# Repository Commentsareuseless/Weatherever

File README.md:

# Weather-ever
Simple weather station, to monitor wind speed, temperature and humidity

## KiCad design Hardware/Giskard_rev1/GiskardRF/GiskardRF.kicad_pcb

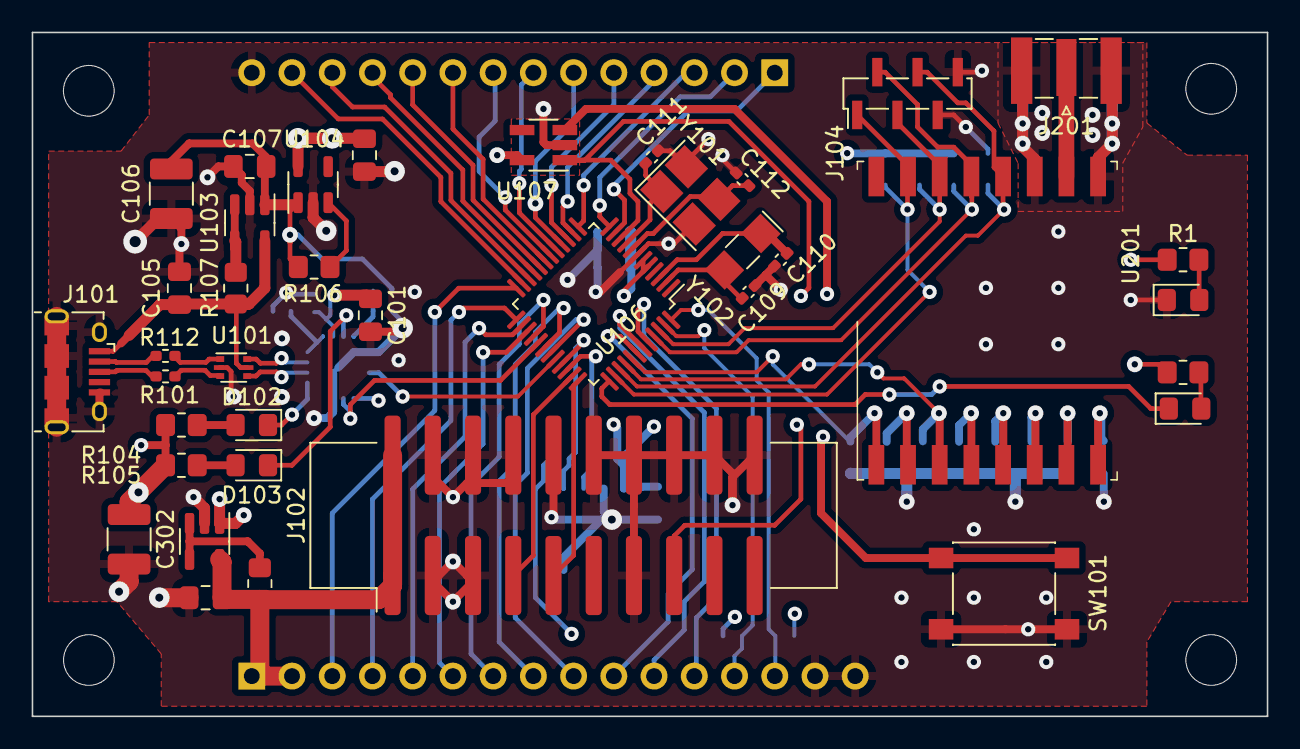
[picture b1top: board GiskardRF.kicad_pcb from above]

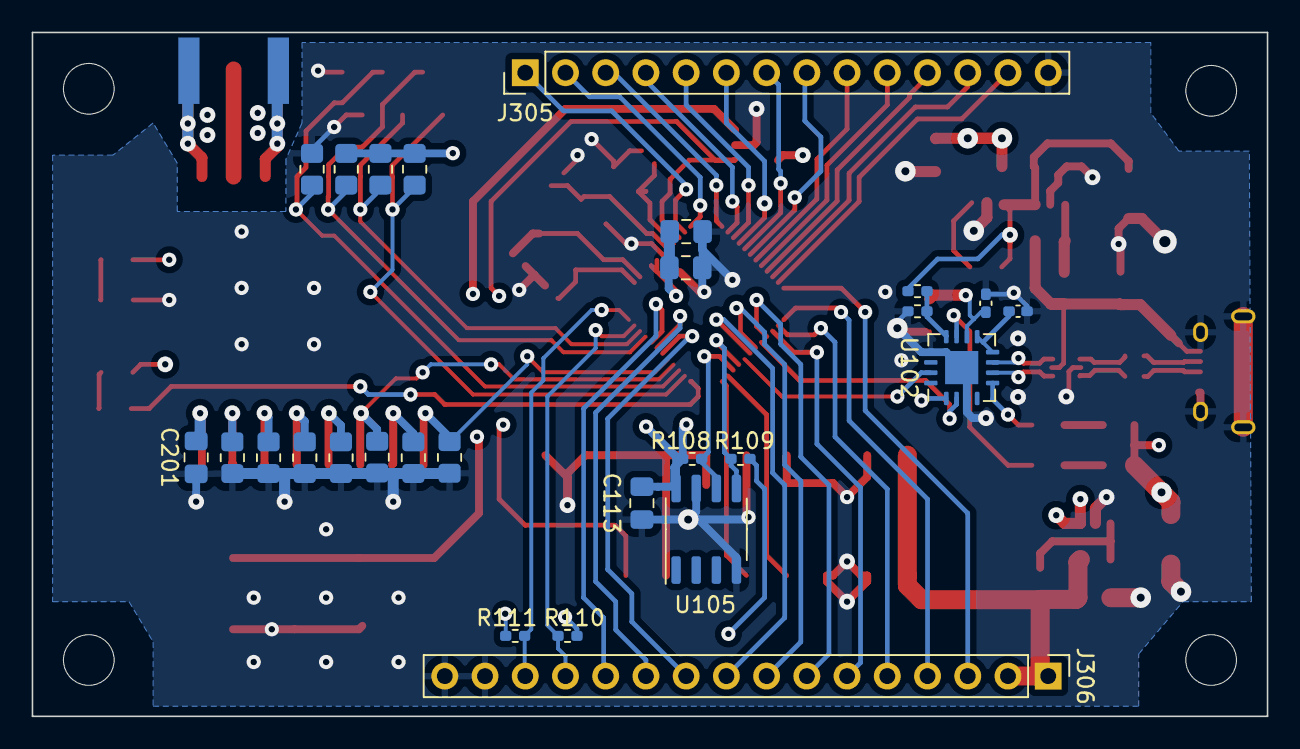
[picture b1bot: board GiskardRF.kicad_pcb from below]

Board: 4 copper layers, 78.0 x 43.2 mm, 69 parts (27 on the bottom side), 72 nets.

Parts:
C101: 4u7; C_0805_2012Metric_Pad1.18x1.45mm_HandSolder
C102, C104: 100n; C_0402_1005Metric_Pad0.74x0.62mm_HandSolder
C105, C108, C301: 1u; C_0805_2012Metric_Pad1.18x1.45mm_HandSolder
C106, C302: 100u; C_1210_3225Metric_Pad1.33x2.70mm_HandSolder
C107, C113, C115, C201: 100n; C_0805_2012Metric_Pad1.18x1.45mm_HandSolder
C109, C110: 20p; C_0402_1005Metric_Pad0.74x0.62mm_HandSolder
C111, C112: 13p; C_0402_1005Metric_Pad0.74x0.62mm_HandSolder
C114: 10u; C_0805_2012Metric_Pad1.18x1.45mm_HandSolder
D1: PWR_LED; D_0805_2012Metric_Pad1.15x1.40mm_HandSolder
D101: ERR_LED; D_0805_2012Metric_Pad1.15x1.40mm_HandSolder
D102: RX_LED; D_0805_2012Metric_Pad1.15x1.40mm_HandSolder
D103: TX_LED; D_0805_2012Metric_Pad1.15x1.40mm_HandSolder
H101, H102, H103, H104: MountingHole; MountingHole_3.2mm_M3
J101: USB_B_Micro; USB_Micro-B_Amphenol_10118194_Horizontal
J102: Conn_ARM_JTAG_SWD_20; IDC-Header_2x10_P2.54mm_Vertical_SMD
J104: Test pins COMM1; PinSocket_1x06_P1.27mm_Vertical_SMD_Pin1Left
J201: SMA6252A23G50; SMA_Samtec_SMA-J-P-X-ST-EM1_EdgeMount
J305: Conn_01x14; PinHeader_1x14_P2.54mm_Vertical
J306: Conn_01x16; PinHeader_1x16_P2.54mm_Vertical
R1, R102, R104, R105: 330; R_0805_2012Metric_Pad1.20x1.40mm_HandSolder
R101, R112: 27; R_0402_1005Metric_Pad0.72x0.64mm_HandSolder
R103: 4k7; R_0402_1005Metric_Pad0.72x0.64mm_HandSolder
R106: 2k; R_0805_2012Metric_Pad1.20x1.40mm_HandSolder
R107, R301: 10k; R_0805_2012Metric_Pad1.20x1.40mm_HandSolder
R108, R109, R110, R111: 3k3; R_0402_1005Metric_Pad0.72x0.64mm_HandSolder
R113: 10k; R_0402_1005Metric_Pad0.72x0.64mm_HandSolder
R201, R202, R203, R204, R206, R207, R208, R209, R210, R211: 20k; R_0805_2012Metric_Pad1.20x1.40mm_HandSolder
R205: 51k; R_0805_2012Metric_Pad1.20x1.40mm_HandSolder
SW101: RESET; SW_Push_1P1T_NO_6x6mm_H9.5mm
U101: USBLC6-2P6; SOT-666
U102: FT230XQ; QFN-16-1EP_4x4mm_P0.65mm_EP2.1x2.1mm
U103, U303: AP22802AW5-7; SOT-23-5
U104: AP2127K-3.3; SOT-23-5
U105: M24C16-RM; SO-8_3.9x4.9mm_P1.27mm
U106: STM32G070CBTx; LQFP-48_7x7mm_P0.5mm
U107: APX823; SOT-23-5_HandSoldering
U201: RFM69HW; HOPERF_RFM69HW
Y101: 3225-16M-SR 16MHz 9pF; Crystal_SMD_SeikoEpson_FA238-4Pin_3.2x2.5mm_HandSoldering
Y102: 32.768K-CFPX217; Crystal_SMD_MicroCrystal_CC7V-T1A-2Pin_3.2x1.5mm_HandSolder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

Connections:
+3V3: C101.1, C102.1, C108.1, C113.1, C114.1, C115.1, C201.2, C302.1, R1.1, R102.1, R104.1, R105.1, R108.1, R109.1, R110.1, R111.1, R202.1, R203.1, R204.1, U102.1 (VCCIO), U102.10 (VCC), U104.5 (VOUT), U105.8 (VCC), U106.5 (VREF+), U106.6 (VDD), U107.5 (VCC), U201.8 (3.3V), U303.1 (OUT)
+5V: C106.1, C107.1, R103.1, R106.2, U103.1 (OUT), U104.1 (VIN)
/5V_USB: C105.1, J101.1 (VBUS), R107.1, U101.5 (VBUS), U103.5 (IN)
/CON_PWR: C301.1, J102.1 (VTREF), J102.2 (VCC/NC), J306.1, J306.2, R301.1, U303.5 (IN)
/GPIO_PA0: J305.1, U106.11 (PA0)
/GPIO_PA1: J305.2, U106.12 (PA1)
/GPIO_PA2: J305.3, U106.13 (PA2)
/GPIO_PA3: J305.4, U106.14 (PA3)
/GPIO_PA4: J305.5, U106.15 (PA4)
/GPIO_PA8: J306.7, U106.28 (PA8)
/GPIO_PB0: J305.9, U106.19 (PB0)
/GPIO_PB1: J305.10, U106.20 (PB1)
/GPIO_PB2: J305.11, U106.21 (PB2)
/GPIO_PB3: J306.10, U106.42 (PB3)
/GPIO_PB4: J306.11, U106.43 (PB4)
/GPIO_PB5: J306.12, U106.44 (PB5)
/GPIO_PB10: J305.12, U106.22 (PB10)
/GPIO_PB11: J305.13, U106.23 (PB11)
/GPIO_PB12: J306.3, U106.24 (PB12)
/GPIO_PB13: J306.4, U106.25 (PB13)
/GPIO_PB14: J306.5, U106.26 (PB14)
/GPIO_PB15: J306.6, U106.27 (PB15)
/GPIO_PC6: J306.8, U106.30 (PC6)
/GPIO_PC7: J306.9, U106.31 (PC7)
/HF_OSC_IN: C112.1, U106.8 (PF0), Y101.3
/HF_OSC_OUT: C111.1, U106.9 (PF1), Y101.1
/I2C1_SCL: J306.13, R110.2, U106.47 (PB8)
/I2C1_SDA: J306.14, R111.2, U106.48 (PB9)
/I2C2_SCL_MEM: R109.2, U105.5 (SDA), U106.33 (PA11/PA9)
/I2C2_SDA_MEM: R108.2, U105.6 (SCL), U106.34 (PA12/PA10)
/LF_OSC_IN: C109.1, U106.2 (PC14), Y102.2
/LF_OSC_OUT: C110.1, U106.3 (PC15), Y102.1
/RF_FIFO_F_NE: R207.2, U106.40 (PD2), U201.3 (DIO1)
/RF_RESET: R205.2, U106.41 (PD3), U201.1 (RESET)
/RX_LED: D102.1 (K), U102.5 (CBUS2)
/RadioComm1/ANT_OUT: J201.1 (In), U201.10 (ANA)
/RadioComm1/RF_DIO0: R206.2, U201.2 (DIO0)
/RadioComm1/RF_DIO2: R208.2, U201.4 (DIO2)
/RadioComm1/RF_DIO3: R209.2, U201.5 (DIO3)
/RadioComm1/RF_DIO4: R210.2, U201.6 (DIO4)
/RadioComm1/RF_DIO5: R211.2, U201.7 (DIO5)
/SPI1_MISO: J305.7, U106.17 (PA6)
/SPI1_MOSI: J305.8, U106.18 (PA7)
/SPI1_SCK: J305.6, U106.16 (PA5)
/SPI2_MISO: J104.2, R202.2, U106.45 (PB6), U201.13 (MISO)
/SPI2_MOSI: J104.3, R203.2, U106.46 (PB7), U201.14 (MOSI)
/SPI2_NSS: J104.1, R204.2, U106.38 (PD0), U201.15 (NSS)
/SPI2_SCK: J104.4, R201.2, U106.39 (PD1), U201.12 (SCK)
/SW_CLK: J102.9 (TCK/SWDCLK), U106.36 (PA14)
/SW_DIO: J102.7 (TMS/SWDIO), U106.35 (PA13)
/TX_LED: D103.1 (K), U102.11 (CBUS1)
/USART1_RX: U102.15 (TXD), U106.32 (PA10/NC)
/USART1_TX: U102.2 (RXD), U106.29 (PA9/NC)
/USB_D+: J101.3 (D+), R101.2
/USB_D-: J101.2 (D-), R112.1
/USB_D_S+: U101.4 (I/O2), U102.6 (USBDP)
/USB_D_S-: U101.6 (I/O1), U102.7 (USBDM)
/USB_RES+: R101.1, U101.3 (I/O2)
/USB_RES-: R112.2, U101.1 (I/O1)
/~ERR_LED: D101.1 (K), U106.37 (PA15)
/~RESET: J102.15 (~SRST), U106.10 (NRST), U107.1 (~RESET)
GNDD: C101.2, C102.2, C104.2, C105.2, C106.2, C107.2, C108.2, C109.2, C110.2, C111.2, C112.2, C113.2, C114.2, C115.2, C201.1, C301.2, C302.2, D1.1 (K), J101.5 (GND), J101.6 (Shield), J102.3 (~TRST), J102.4 (GND), J102.5 (TDI), J102.6 (GND), J102.8 (GND), J102.10 (GND), J102.12 (GND), J102.13 (TDO/SWO), J102.14 (GND), J102.16 (GND), J102.18 (GND), J102.20 (GND), J104.5, J104.6, J201.2 (Ext), J305.14, J306.15, J306.16, R113.2, R201.1, R205.1, R206.1, R207.1, R208.1, R209.1, R210.1, R211.1, SW101.1, SW101.2, U101.2 (GND), U102.3 (GND), U102.13 (GND), U102.17 (GND), U103.2 (GND), U104.2 (GND), U105.4 (GND), U105.7 (~WC), U106.7 (VSS), U107.2 (GND), U201.9 (GND), U201.11 (GND), U303.2 (GND), Y101.2, Y101.4
unnamed: D1.2 (A), R1.2
unnamed: D101.2 (A), R102.2
unnamed: D102.2 (A), R104.2
unnamed: D103.2 (A), R105.2
unnamed: SW101.3 (K), SW101.4 (A), U107.3 (~MR)
unnamed: C104.1, U102.8 (3V3OUT), U102.9 (~RESET)
unnamed: R103.2, R113.1, U102.12 (CBUS0)
unnamed: R107.2, U103.3 (~FLG), U103.4 (EN)
unnamed: R106.1, U104.3 (EN)
unnamed: R301.2, U303.3 (~FLG), U303.4 (EN)

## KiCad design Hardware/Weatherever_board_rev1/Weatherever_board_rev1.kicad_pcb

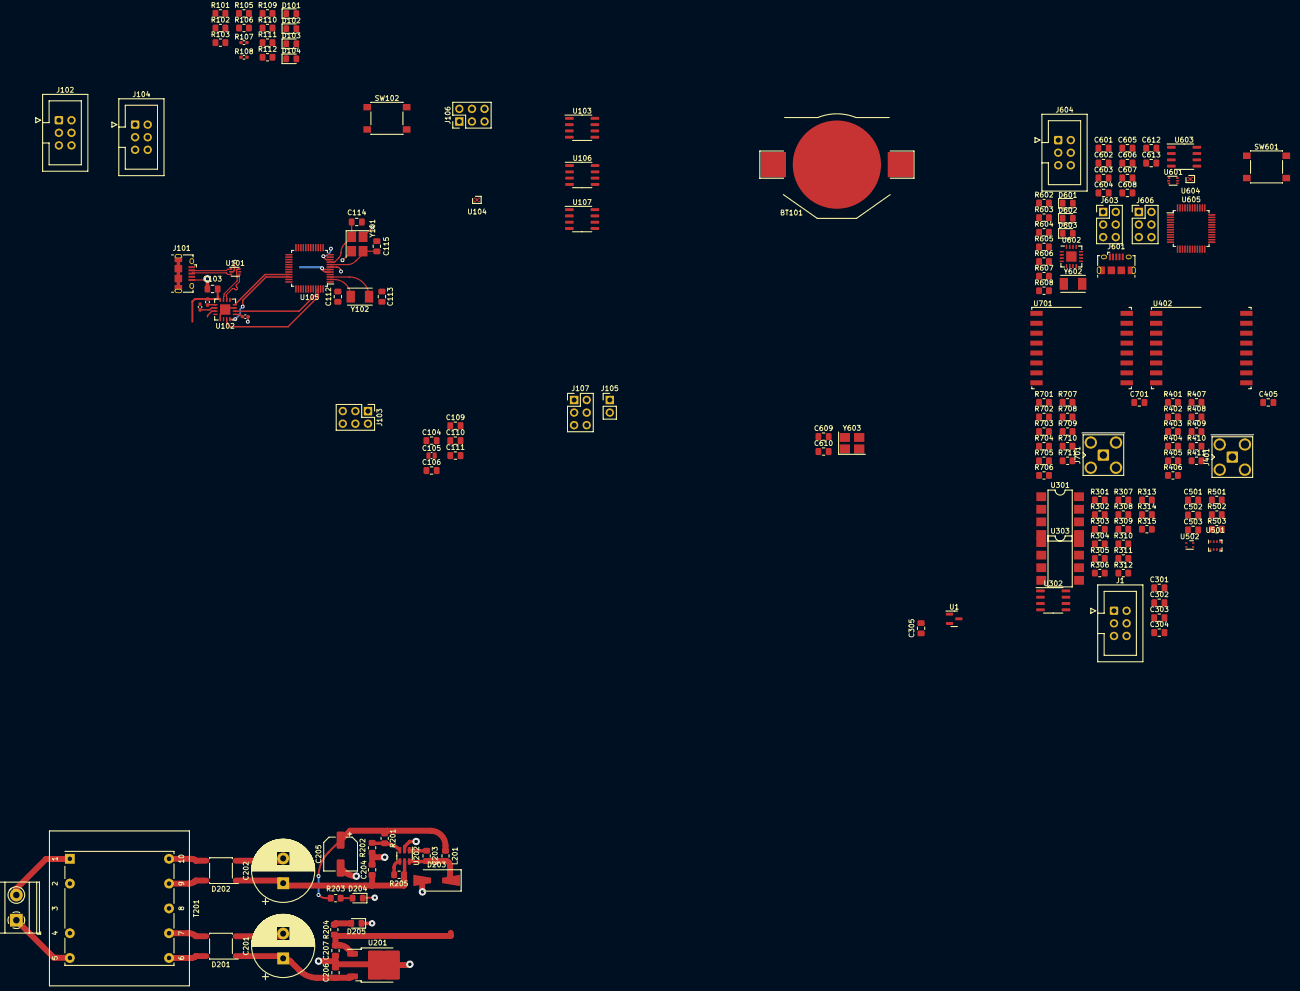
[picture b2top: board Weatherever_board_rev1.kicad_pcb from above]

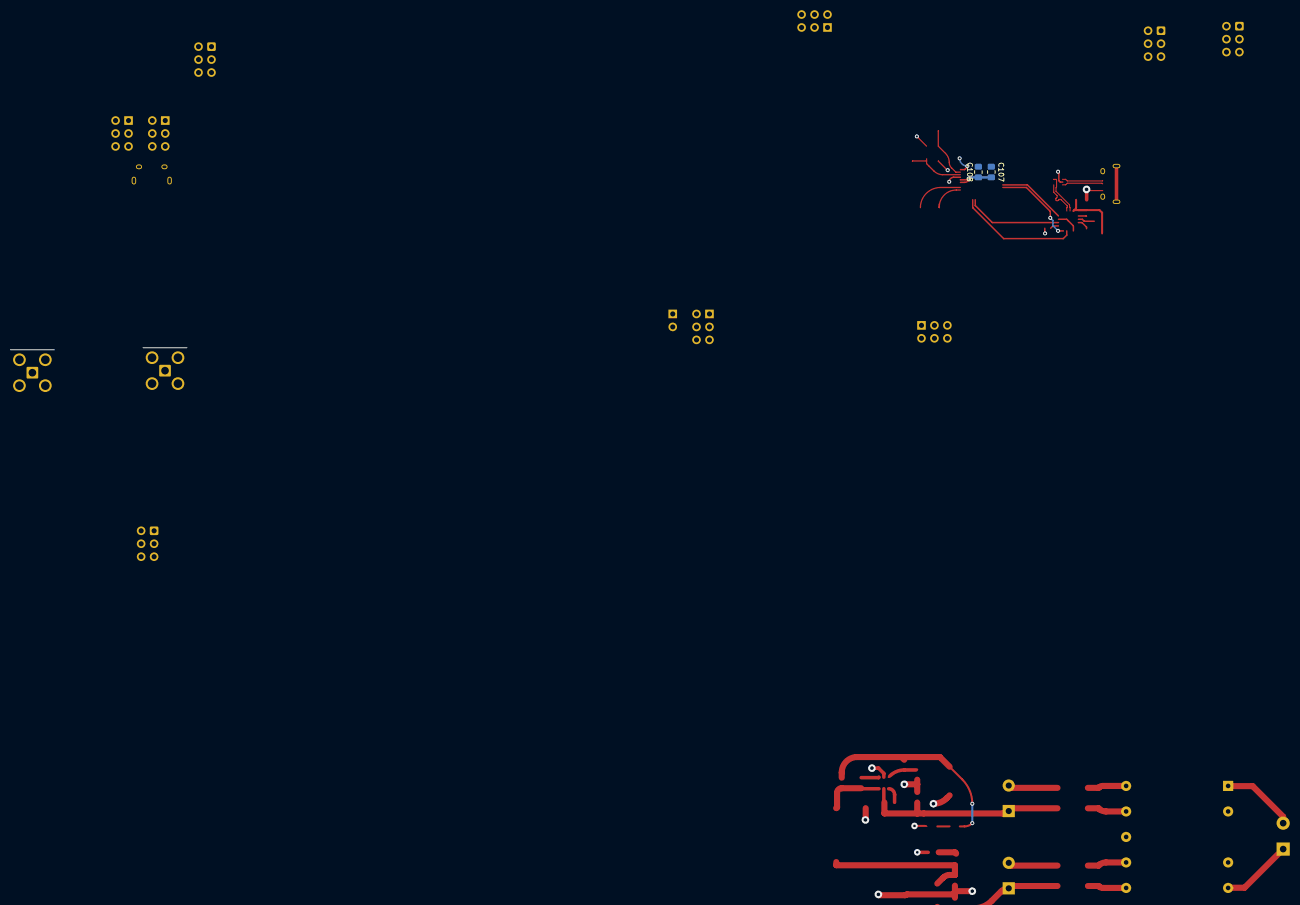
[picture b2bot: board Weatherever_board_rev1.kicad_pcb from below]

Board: 2 copper layers, 171 parts (2 on the bottom side), 118 nets.

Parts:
BT101: RTC_Bat; BatteryHolder_Keystone_3002_1x2032
C101, C102: 100n; C_0402_1005Metric_Pad0.74x0.62mm_HandSolder
C103, C106, C603, C606: 1u; C_0805_2012Metric_Pad1.18x1.45mm_HandSolder
C104, C107, C204, C604, C607: 10u; C_0805_2012Metric_Pad1.18x1.45mm_HandSolder
C105: 100n; C_0504_1310Metric_Pad0.83x1.28mm_HandSolder
C108, C109, C110, C111, C112, C113, C114, C115, C207, C301, C303, C305, C405, C501, C502, C503, C601, C602, C605, C608, C609, C610, C612, C613, C701: 100n; C_0805_2012Metric_Pad1.18x1.45mm_HandSolder
C201, C202: 1500u; CP_Radial_D12.5mm_P5.00mm
C203, C302, C304: 10n; C_0805_2012Metric_Pad1.18x1.45mm_HandSolder
C205: 100u; CP_Elec_6.3x5.4
C206: 330n; C_0805_2012Metric_Pad1.18x1.45mm_HandSolder
D101, D601: ERR_LED (RED); D_0805_2012Metric_Pad1.15x1.40mm_HandSolder
D102, D602: RX_LED; D_0805_2012Metric_Pad1.15x1.40mm_HandSolder
D103, D603: TX_LED; D_0805_2012Metric_Pad1.15x1.40mm_HandSolder
D104: CPU_PWR; D_0805_2012Metric_Pad1.15x1.40mm_HandSolder
D201, D202: AB4S; Diode_Bridge_Diotec_ABS
D203: STS130A; D_SMA-SMB_Universal_Handsoldering
D204: PWR_3V3; LED_0805_2012Metric_Pad1.15x1.40mm_HandSolder
D205: PWR_9V; LED_0805_2012Metric_Pad1.15x1.40mm_HandSolder
H101, H102, H103, H104, H105: MountingHole; MountingHole_3.2mm_M3
J1: ProbeConn; IDC-Header_2x03_P2.54mm_Vertical
J101, J601: USB_B_Micro; USB_Micro-B_Amphenol_10118194_Horizontal
J102: Expansion conn; IDC-Header_2x03_P2.54mm_Vertical
J103, J603: Test pins COMM1; PinHeader_2x03_P2.54mm_Vertical
J104, J604: DebugConn; IDC-Header_2x03_P2.54mm_Vertical
J105: Test pins Probe; PinHeader_1x02_P2.54mm_Vertical
J106, J606: Test pins COMM2; PinHeader_2x03_P2.54mm_Vertical
J107: Test pins I2C; PinHeader_2x03_P2.54mm_Vertical
J201: Mains (230V, 50Hz); TerminalBlock_Phoenix_MKDS-1,5-2-5.08_1x02_P5.08mm_Horizont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
J401, J701: SMA6252A23G50; SMA_Amphenol_901-143_Horizontal
L201: 2u2; L_0805_2012Metric_Pad1.15x1.40mm_HandSolder
R101, R103, R105, R106, R203, R603, R605, R606: 270; R_0805_2012Metric_Pad1.20x1.40mm_HandSolder
R102, R302, R501, R502, R503, R602, R604, R607: 2k; R_0805_2012Metric_Pad1.20x1.40mm_HandSolder
R104, R107: 2k; R_0402_1005Metric_Pad0.72x0.64mm_HandSolder
R108: 10k; R_0402_1005Metric_Pad0.72x0.64mm_HandSolder
R109, R110, R111, R112, R303, R310: 3k3; R_0805_2012Metric_Pad1.20x1.40mm_HandSolder
R201: 51k1; R_0805_2012Metric_Pad1.20x1.40mm_HandSolder
R202: 16k2; R_0805_2012Metric_Pad1.20x1.40mm_HandSolder
R204: 1k; R_0805_2012Metric_Pad1.20x1.40mm_HandSolder
R205, R608: 10k; R_0805_2012Metric_Pad1.20x1.40mm_HandSolder
R301: 330; R_0805_2012Metric_Pad1.20x1.40mm_HandSolder
R304, R313, R411, R705: 51k; R_0805_2012Metric_Pad1.20x1.40mm_HandSolder
R305, R306, R308, R309, R311, R314, R315, R401, R402, R403, R404, R405, R406, R407, R408, R409, R410, R701, R702, R703, R704, R706, R707, R708, R709, R710, R711: 20k; R_0805_2012Metric_Pad1.20x1.40mm_HandSolder
R307, R312: 100k; R_0805_2012Metric_Pad1.20x1.40mm_HandSolder
SW102, SW601: RESET; SW_Push_1P1T_NO_6x6mm_H9.5mm
T201: TEZ2.5/D230/10.5-10.5V; Transformer_Breve_TEZ-28x33
U1: ZXCT1009F; SOT-23
U101, U601: USBLC6-2P6; SOT-666
U102, U602: FT230XQ; QFN-16-1EP_4x4mm_P0.65mm_EP2.1x2.1mm
U103, U603: AOZ1312; SO-8_3.9x4.9mm_P1.27mm
U104, U604: NCP115AMX250TCG; OnSemi_XDFN4-1EP_1.0x1.0mm_EP0.52x0.52mm
U105, U605: STM32G030C8T6; LQFP-48_7x7mm_P0.5mm
U106, U107: M24C08-W; SO-8_3.9x4.9mm_P1.27mm
U201: L78M09CDT; TO-252-2
U202: AOZ1280CI; SOT-23-6
U301, U303: 6N137; SMDIP-8_W7.62mm
U302: LM393; SO-8_3.9x4.9mm_P1.27mm
U402, U701: RFM69HW; HOPERF_RFM69HW
U501: DPS310; Bosch_LGA-8_2x2.5mm_P0.65mm_ClockwisePinNumbering
U502: SHT4x; Sensirion_DFN-4_1.5x1.5mm_P0.8mm_SHT4x_NoCentralPad
Y101, Y603: 3225-16M-SR 16MHz 9pF; Crystal_SMD_TXC_7M-4Pin_3.2x2.5mm_HandSoldering
Y102, Y602: 32.768K-CFPX217; Crystal_SMD_TXC_7A-2Pin_5x3.2mm

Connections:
+3V3: C102.1, C103.1, C106.1, C107.1, C108.1, C109.1, C110.1, C205.1, C301.1, C303.1, C405.2, C501.1, C502.1, C503.1, C602.1, C603.1, C606.1, C607.1, C608.1, C701.2, J102.1, J104.1, J104.2, J604.1, J604.2, L201.2, R101.1, R102.1, R103.1, R104.1, R105.1, R106.1, R109.1, R110.1, R111.1, R112.1, R201.1, R203.1, R303.1, R310.1, R402.1, R403.1, R404.1, R501.2, R502.2, R503.2, R602.1, R603.1, R604.1, R605.1, R606.1, R702.1, R703.1, R704.1, U102.1 (VCCIO), U102.8 (3V3OUT), U104.1 (OUT), U105.5 (VREF+), U105.6 (VDD/VDDA), U106.3 (E2), U106.8 (Vcc), U107.8 (Vcc), U301.8 (VCC), U303.8 (VCC), U402.8 (3.3V), U501.6 (VDDIO), U501.8 (VDD), U502.3 (VDD), U602.1 (VCCIO), U602.8 (3V3OUT), U604.1 (OUT), U605.5 (VREF+), U605.6 (VDD/VDDA), U701.8 (3.3V)
+5V: C101.1, C105.1, C601.1, C605.1, R107.2, R607.2, U102.10 (VCC), U103.7 (OUT), U104.4 (IN), U602.10 (VCC), U603.7 (OUT), U604.4 (IN)
+9V: C207.1, C305.2, J102.5, R204.1, R301.1, R304.1, R305.1, R306.1, R311.1, R313.1, U1.2 (Vs+), U201.1 (OUT), U302.8 (V+)
/3V_Bat: BT101.1 (+), C111.1, U105.4 (VBAT)
/5V_USB: J101.1 (VBUS), R108.1, U101.5 (VBUS), U103.2 (IN), U103.4 (EN)
/CONN_VALID: R310.2, U105.39 (PD1), U303.6 (VO), U303.7 (EN)
/HF_OSC_IN: C115.1, U105.8 (PF0-OSC_IN), Y101.3
/HF_OSC_OUT: C114.1, U105.9 (PF1-OSC_OUT), Y101.1
/I2C1_SCL: J107.5, R111.2, R501.1, U105.29 (PA9), U501.4 (SCK), U502.2 (SCL)
/I2C1_SDA: J107.6, R112.2, R502.1, U105.32 (PA10), U501.3 (SDI), U502.1 (SDA)
/I2C2_SCL_MEM: J107.1, R109.2, R110.2, U105.25 (PB13), U106.6 (SCL), U107.6 (SCL)
/I2C2_SDA_MEM: J107.2, U105.26 (PB14), U106.5 (SDA), U107.5 (SDA)
/IsolatedFreqCnt/ConnCheck-: J1.1, J1.2, R301.2, U1.1 (Vs-)
/IsolatedFreqCnt/CurrentOut: R302.1, R314.2, U1.3 (Iout)
/IsolatedFreqCnt/NPN_OUT: J1.4, R304.2, R308.2
/LF_OSC_IN: C112.1, U105.2 (PC14-OSC32_IN), Y102.2
/LF_OSC_OUT: C113.1, U105.3 (PC15-OSC32_OUT), Y102.1
/PRS_RDY: U105.41 (PD3), U501.5 (SDO)
/PowerSupply/10V5AC_HI1: D201.4, T201.6 (SA)
/PowerSupply/10V5AC_HI2: D201.3, T201.7 (SB)
/PowerSupply/10V5AC_LO1: D202.4, T201.9 (SC)
/PowerSupply/10V5AC_LO2: D202.3, T201.10 (SD)
/PowerSupply/~15V_HI: C201.1, C206.1, D201.1 (+), U201.3 (IN)
/PowerSupply/~15V_LO: C202.1, C204.1, D202.1 (+), R205.1, U202.5 (VIN)
/RF_DIO_0: R409.2, U105.21 (PB2), U402.2 (DIO0)
/RF_DIO_1: R408.2, U105.22 (PB10), U402.3 (DIO1)
/RF_DIO_2: R407.2, U105.23 (PB11), U402.4 (DIO2)
/RF_DIO_3: R406.2, U105.24 (PB12), U402.5 (DIO3)
/RF_DIO_4: R405.2, U105.44 (PB5), U402.6 (DIO4)
/RF_DIO_5: R410.2, U105.43 (PB4), U402.7 (DIO5)
/RX_LED: D102.1 (K), U102.5 (CBUS2)
/RadioComm/ANT_OUT: J401.1 (In), U402.10 (ANA)
/RadioComm/RF_RESET: R411.2, U402.1 (RESET)
/SPI1_CS1: J103.2, R404.2, U105.19 (PB0), U402.15 (NSS)
/SPI1_CS2: J103.1, U105.20 (PB1)
/SPI1_MISO: J103.4, U105.17 (PA6), U402.13 (MISO)
/SPI1_MOSI: J103.3, R402.2, R403.2, U105.18 (PA7), U402.14 (MOSI)
/SPI1_SCK: J103.5, R401.2, U105.16 (PA5), U402.12 (SCK)
/SW_CLK: J104.3, U105.36 (PA14-BOOT0)
/SW_DIO: J104.4, U105.35 (PA13)
/TIM_IN: J105.1, R303.2, U105.38 (PD0), U301.6 (VO), U301.7 (EN)
/TX_LED: D103.1 (K), U102.11 (CBUS1)
/USART1_CTS: J106.4, U102.4 (~CTS), U105.33 (PA11)
/USART1_RTS: J106.3, U102.16 (~RTS), U105.34 (PA12)
/USART1_RX: J106.2, U102.15 (TXD), U105.46 (PB7)
/USART1_TX: J106.1, U102.2 (RXD), U105.45 (PB6)
/USART2_RX: J102.4, U105.14 (PA3)
/USART2_TX: J102.3, U105.13 (PA2)
/USB_D+: J101.3 (D+), U101.3 (I/O2)
/USB_D-: J101.2 (D-), U101.1 (I/O1)
/USB_D_S+: U101.4 (I/O2), U102.6 (USBDP)
/USB_D_S-: U101.6 (I/O1), U102.7 (USBDM)
/USB_Dongle/5V_USB: J601.1 (VBUS), R608.1, U601.5 (VBUS), U603.2 (IN), U603.4 (EN)
/USB_Dongle/HF_OSC_IN: C610.1, U605.8 (PF0-OSC_IN), Y603.3
/USB_Dongle/HF_OSC_OUT: C609.1, U605.9 (PF1-OSC_OUT), Y603.1
/USB_Dongle/LF_OSC_IN: C612.1, U605.2 (PC14-OSC32_IN), Y602.2
/USB_Dongle/LF_OSC_OUT: C613.1, U605.3 (PC15-OSC32_OUT), Y602.1
/USB_Dongle/RF_DIO_0: R706.2, U605.21 (PB2), U701.2 (DIO0)
/USB_Dongle/RF_DIO_1: R707.2, U605.22 (PB10), U701.3 (DIO1)
/USB_Dongle/RF_DIO_2: R708.2, U605.23 (PB11), U701.4 (DIO2)
/USB_Dongle/RF_DIO_3: R709.2, U605.24 (PB12), U701.5 (DIO3)
/USB_Dongle/RF_DIO_4: R710.2, U605.44 (PB5), U701.6 (DIO4)
/USB_Dongle/RF_DIO_5: R711.2, U605.43 (PB4), U701.7 (DIO5)
/USB_Dongle/RX_LED: D602.1 (K), U602.5 (CBUS2)
/USB_Dongle/RadioComm1/ANT_OUT: J701.1 (In), U701.10 (ANA)
/USB_Dongle/RadioComm1/RF_RESET: R705.2, U701.1 (RESET)
/USB_Dongle/SPI1_CS1: J603.2, R704.2, U605.19 (PB0), U701.15 (NSS)
/USB_Dongle/SPI1_CS2: J603.1, U605.20 (PB1)
/USB_Dongle/SPI1_MISO: J603.4, U605.17 (PA6), U701.13 (MISO)
/USB_Dongle/SPI1_MOSI: J603.3, R702.2, R703.2, U605.18 (PA7), U701.14 (MOSI)
/USB_Dongle/SPI1_SCK: J603.5, R701.2, U605.16 (PA5), U701.12 (SCK)
/USB_Dongle/SW_CLK: J604.3, U605.36 (PA14-BOOT0)
/USB_Dongle/SW_DIO: J604.4, U605.35 (PA13)
/USB_Dongle/TX_LED: D603.1 (K), U602.11 (CBUS1)
/USB_Dongle/USART1_CTS: J606.4, U602.4 (~CTS), U605.33 (PA11)
/USB_Dongle/USART1_RTS: J606.3, U602.16 (~RTS), U605.34 (PA12)
/USB_Dongle/USART1_RX: J606.2, U602.15 (TXD), U605.46 (PB7)
/USB_Dongle/USART1_TX: J606.1, U602.2 (RXD), U605.45 (PB6)
/USB_Dongle/USB_D+: J601.3 (D+), U601.4 (I/O2)
/USB_Dongle/USB_D-: J601.2 (D-), U601.6 (I/O1)
/USB_Dongle/USB_D_S+: U601.3 (I/O2), U602.6 (USBDP)
/USB_Dongle/USB_D_S-: U601.1 (I/O1), U602.7 (USBDM)
/USB_Dongle/~ERR_LED: D601.1 (K), U605.40 (PD2)
/USB_Dongle/~RESET: C604.1, R602.2, SW601.2, U605.10 (NRST)
/~ERR_LED: D101.1 (K), U105.40 (PD2)
/~RESET: C104.1, R102.2, SW102.2, U105.10 (NRST)
GND1: C201.2, C206.2, C207.2, C305.1, D201.2 (-), D205.1 (K), J1.5, J1.6, J102.6, R302.2, R309.2, R315.2, U201.2 (GND), U302.4 (V-)
GNDD: BT101.2 (-), C101.2, C102.2, C103.2, C104.2, C105.2, C106.2, C107.2, C108.2, C109.2, C110.2, C111.2, C112.2, C113.2, C114.2, C115.2, C202.2, C204.2, C205.2, C301.2, C303.2, C405.1, C501.2, C502.2, C503.2, C601.2, C602.2, C603.2, C604.2, C605.2, C606.2, C607.2, C608.2, C609.2, C610.2, C612.2, C613.2, C701.1, D104.1 (K), D202.2 (-), D203.2 (A), D204.1 (K), J101.5 (GND), J101.6 (Shield), J102.2, J103.6, J104.5, J104.6, J105.2, J106.6, J107.3, J107.4, J401.2 (Ext), J601.5 (GND), J601.6 (Shield), J603.6, J604.5, J604.6, J606.6, J701.2 (Ext), R202.2, R401.1, R405.1, R406.1, R407.1, R408.1, R409.1, R410.1, R411.1, R701.1, R705.1, R706.1, R707.1, R708.1, R709.1, R710.1, R711.1, SW102.1, SW601.1, U101.2 (GND), U102.3 (GND), U102.13 (GND), U102.17 (GND), U103.1 (GND), U104.2 (GND), U104.5 (GND), U105.7 (VSS/VSSA), U106.4 (Vss), U106.7 (WC), U107.3 (E2), U107.4 (Vss), U107.7 (WC), U202.2 (GND), U301.5 (GND), U303.5 (GND), U402.9 (GND), U402.11 (GND), U501.1 (GND), U501.7 (GND), U502.4 (VSS), U601.2 (GND), U602.3 (GND), U602.13 (GND), U602.17 (GND), U603.1 (GND), U604.2 (GND), U604.5 (GND), U605.7 (VSS/VSSA), U701.9 (GND), U701.11 (GND), Y101.2, Y101.4, Y603.2, Y603.4
unnamed: D101.2 (A), R103.2
unnamed: D102.2 (A), R105.2
unnamed: D103.2 (A), R106.2
unnamed: D104.2 (A), R101.2
unnamed: C203.2, D203.1 (K), L201.1, U202.6 (LX)
unnamed: D204.2 (A), R203.2
unnamed: D205.2 (A), R204.2
unnamed: D601.2 (A), R603.2
unnamed: D602.2 (A), R605.2
unnamed: D603.2 (A), R606.2
unnamed: J201.1, T201.5 (AB)
unnamed: J201.2, T201.1 (AA)
unnamed: R104.2, U102.9 (~RESET)
unnamed: R108.2, U103.5 (~OC)
unnamed: R107.1, U104.3 (EN)
unnamed: C203.1, U202.1 (BST)
unnamed: R205.2, U202.4 (EN)
unnamed: R201.2, R202.1, U202.3 (FB)
unnamed: R306.2, U301.2 (A)
unnamed: C302.1, R307.1, U301.3 (C), U302.7
unnamed: C304.2, R312.2, R314.1, U302.3 (+)
unnamed: R313.2, R315.1, U302.2 (-)
unnamed: C302.2, R307.2, R308.1, U302.5 (+)
unnamed: R305.2, R309.1, U302.6 (_)
unnamed: R311.2, U303.2 (A)
unnamed: C304.1, R312.1, U302.1, U303.3 (C)
unnamed: R503.1, U501.2 (CSB)
unnamed: R604.2, U602.9 (~RESET)
unnamed: R608.2, U603.5 (~OC)
unnamed: R607.1, U604.3 (EN)

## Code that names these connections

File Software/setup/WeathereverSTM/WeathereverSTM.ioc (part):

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Mcu.Name=STM32G030C(6-8)Tx
Mcu.Package=LQFP48
Mcu.UserName=STM32G030C8Tx
PA10.GPIOParameters=GPIO_Pu
PA10.GPIO_Pu=GPIO_PULLUP
PA10.Mode=I2C
PA10.Signal=I2C1_SDA
PA11\ [PA9].Mode=CTS_RTS
PA11\ [PA9].Signal=USART1_CTS
PA12\ [PA10].Mode=CTS_RTS
PA12\ [PA10].Signal=USART1_RTS
PA13.Mode=Serial_Wire
PA13.Signal=SYS_SWDIO
PA14-BOOT0.Mode=Serial_Wire
PA14-BOOT0.Signal=SYS_SWCLK
PA2.Mode=Asynchronous
PA2.Signal=USART2_TX
PA3.Mode=Asynchronous
PA3.Signal=USART2_RX
PA5.Mode=Full_Duplex_Master
PA5.Signal=SPI1_SCK
PA6.Mode=Full_Duplex_Master
PA6.Signal=SPI1_MISO
PA7.Mode=Full_Duplex_Master
PA7.Signal=SPI1_MOSI
PA9.GPIOParameters=GPIO_Pu
PA9.GPIO_Pu=GPIO_PULLUP
PA9.Mode=I2C
PA9.Signal=I2C1_SCL
PB0.Signal=GPIO_Output
PB1.Signal=GPIO_Output
PB10.Signal=GPIO_Input
PB13.GPIOParameters=GPIO_Pu
PB13.GPIO_Pu=GPIO_PULLUP
PB13.Mode=I2C
PB13.Signal=I2C2_SCL
PB14.GPIOParameters=GPIO_Pu
PB14.GPIO_Pu=GPIO_PULLUP
PB14.Mode=I2C
PB14.Signal=I2C2_SDA
PB2.Signal=GPIO_Input
PB3.Signal=GPIO_Input
PB6.Mode=Asynchronous
PB6.Signal=USART1_TX
PB7.Mode=Asynchronous
PB7.Signal=USART1_RX
PC14-OSC32_IN\ (PC14).Mode=LSE-External-Oscillator
PC14-OSC32_IN\ (PC14).Signal=RCC_OSC32_IN
PC15-OSC32_OUT\ (PC15).Mode=LSE-External-Oscillator
PC15-OSC32_OUT\ (PC15).Signal=RCC_OSC32_OUT
PD0.Signal=S_TIM16_CH1
PD1.Signal=GPIO_Input
PD2.Signal=GPIO_Input
PD3.Signal=GPIO_Input
PF0-OSC_IN\ (PF0).Mode=HSE-External-Oscillator
PF0-OSC_IN\ (PF0).Signal=RCC_OSC_IN
PF1-OSC_OUT\ (PF1).Mode=HSE-External-Oscillator
PF1-OSC_OUT\ (PF1).Signal=RCC_OSC_OUT
RCC.HSE_VALUE=16000000
RCC.SYSCLKFreq_VALUE=32000000
RCC.SYSCLKSource=RCC_SYSCLKSOURCE_PLLCLK
board=custom

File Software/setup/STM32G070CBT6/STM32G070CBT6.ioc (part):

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Mcu.Name=STM32G070CBTx
Mcu.Package=LQFP48
Mcu.UserName=STM32G070CBTx
PA10.Mode=Asynchronous
PA10.Signal=USART1_RX
PA11\ [PA9].Mode=I2C
PA11\ [PA9].Signal=I2C2_SCL
PA12\ [PA10].Mode=I2C
PA12\ [PA10].Signal=I2C2_SDA
PA13.Mode=Serial_Wire
PA13.Signal=SYS_SWDIO
PA14-BOOT0.Mode=Serial_Wire
PA14-BOOT0.Signal=SYS_SWCLK
PA5.Mode=Full_Duplex_Master
PA5.Signal=SPI1_SCK
PA6.Mode=Full_Duplex_Master
PA6.Signal=SPI1_MISO
PA7.Mode=Full_Duplex_Master
PA7.Signal=SPI1_MOSI
PA9.Mode=Asynchronous
PA9.Signal=USART1_TX
PB6.Mode=Full_Duplex_Master
PB6.Signal=SPI2_MISO
PB7.Mode=Full_Duplex_Master
PB7.Signal=SPI2_MOSI
PB8.Mode=I2C
PB8.Signal=I2C1_SCL
PB9.Mode=I2C
PB9.Signal=I2C1_SDA
PC14-OSC32_IN\ (PC14).Mode=LSE-External-Oscillator
PC14-OSC32_IN\ (PC14).Signal=RCC_OSC32_IN
PC15-OSC32_OUT\ (PC15).Mode=LSE-External-Oscillator
PC15-OSC32_OUT\ (PC15).Signal=RCC_OSC32_OUT
PD0.Mode=NSS_Signal_Hard_Output
PD0.Signal=SPI2_NSS
PD1.Mode=Full_Duplex_Master
PD1.Signal=SPI2_SCK
PF0-OSC_IN\ (PF0).Mode=HSE-External-Oscillator
PF0-OSC_IN\ (PF0).Signal=RCC_OSC_IN
PF1-OSC_OUT\ (PF1).Mode=HSE-External-Oscillator
PF1-OSC_OUT\ (PF1).Signal=RCC_OSC_OUT
RCC.HSE_VALUE=16000000
RCC.SYSCLKFreq_VALUE=64000000
RCC.SYSCLKSource=RCC_SYSCLKSOURCE_PLLCLK
board=custom

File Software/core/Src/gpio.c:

/* USER CODE BEGIN Header */
/**
  ******************************************************************************
  * @file    gpio.c
  * @brief   This file provides code for the configuration
  *          of all used GPIO pins.
  ******************************************************************************
  * @attention
  *
  * Copyright (c) 2023 STMicroelectronics.
  * All rights reserved.
  *
  * This software is licensed under terms that can be found in the LICENSE file
  * in the root directory of this software component.
  * If no LICENSE file comes with this software, it is provided AS-IS.
  *
  ******************************************************************************
  */
/* USER CODE END Header */

/* Includes ------------------------------------------------------------------*/
#include "gpio.h"

/* USER CODE BEGIN 0 */

/* USER CODE END 0 */

/*----------------------------------------------------------------------------*/
/* Configure GPIO                                                             */
/*----------------------------------------------------------------------------*/
/* USER CODE BEGIN 1 */

/* USER CODE END 1 */

/** Configure pins as
        * Analog
        * Input
        * Output
        * EVENT_OUT
        * EXTI
        * Free pins are configured automatically as Analog (this feature is enabled through
        * the Code Generation settings)
*/
void MX_GPIO_Init(void)
{

  GPIO_InitTypeDef GPIO_InitStruct = {0};

  /* GPIO Ports Clock Enable */
  __HAL_RCC_GPIOC_CLK_ENABLE();
  __HAL_RCC_GPIOF_CLK_ENABLE();
  __HAL_RCC_GPIOA_CLK_ENABLE();
  __HAL_RCC_GPIOB_CLK_ENABLE();
  __HAL_RCC_GPIOD_CLK_ENABLE();

  /*Configure GPIO pin Output Level */
  HAL_GPIO_WritePin(GPIOB, GPIO_PIN_0|GPIO_PIN_1, GPIO_PIN_RESET);

  /*Configure GPIO pins : PC13 PC6 PC7 */
  GPIO_InitStruct.Pin = GPIO_PIN_13|GPIO_PIN_6|GPIO_PIN_7;
  GPIO_InitStruct.Mode = GPIO_MODE_ANALOG;
  GPIO_InitStruct.Pull = GPIO_NOPULL;
  HAL_GPIO_Init(GPIOC, &GPIO_InitStruct);

  /*Configure GPIO pins : PA0 PA1 PA4 PA8
                           PA15 */
  GPIO_InitStruct.Pin = GPIO_PIN_0|GPIO_PIN_1|GPIO_PIN_4|GPIO_PIN_8
                          |GPIO_PIN_15;
  GPIO_InitStruct.Mode = GPIO_MODE_ANALOG;
  GPIO_InitStruct.Pull = GPIO_NOPULL;
  HAL_GPIO_Init(GPIOA, &GPIO_InitStruct);

  /*Configure GPIO pins : PB0 PB1 */
  GPIO_InitStruct.Pin = GPIO_PIN_0|GPIO_PIN_1;
  GPIO_InitStruct.Mode = GPIO_MODE_OUTPUT_PP;
  GPIO_InitStruct.Pull = GPIO_NOPULL;
  GPIO_InitStruct.Speed = GPIO_SPEED_FREQ_LOW;
  HAL_GPIO_Init(GPIOB, &GPIO_InitStruct);

  /*Configure GPIO pins : PB2 PB10 PB3 */
  GPIO_InitStruct.Pin = GPIO_PIN_2|GPIO_PIN_10|GPIO_PIN_3;
  GPIO_InitStruct.Mode = GPIO_MODE_INPUT;
  GPIO_InitStruct.Pull = GPIO_NOPULL;
  HAL_GPIO_Init(GPIOB, &GPIO_InitStruct);

  /*Configure GPIO pins : PB11 PB12 PB15 PB4
                           PB5 PB8 PB9 */
  GPIO_InitStruct.Pin = GPIO_PIN_11|GPIO_PIN_12|GPIO_PIN_15|GPIO_PIN_4
                          |GPIO_PIN_5|GPIO_PIN_8|GPIO_PIN_9;
  GPIO_InitStruct.Mode = GPIO_MODE_ANALOG;
  GPIO_InitStruct.Pull = GPIO_NOPULL;
  HAL_GPIO_Init(GPIOB, &GPIO_InitStruct);

  /*Configure GPIO pins : PD1 PD2 PD3 */
  GPIO_InitStruct.Pin = GPIO_PIN_1|GPIO_PIN_2|GPIO_PIN_3;
  GPIO_InitStruct.Mode = GPIO_MODE_INPUT;
  GPIO_InitStruct.Pull = GPIO_NOPULL;
  HAL_GPIO_Init(GPIOD, &GPIO_InitStruct);

}

/* USER CODE BEGIN 2 */

/* USER CODE END 2 */

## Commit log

2023-04-11 Repo innit :)
2023-04-11 minor cleanup
2023-04-16 Finished HW schematic and minor project cleanup
2023-04-16 SW project setup - cmake script rework
2023-04-22 regenerated config and added UT support
2023-04-22 Changed CMake script to move compile_commands.json to CMAKE_SOURCE_DIR after build
2023-04-22 small adjustments to main CMake script and reorganization
2023-06-18 Everythin, sry but I have to :(
2023-06-26 Restructured project, added GTest
2023-06-29 Experimental (not working) changes
2023-06-29 Docs - Project genral idea
2023-07-02 Working artifacts generation
2023-08-26 Some long forgotten changes
    Hope this will not spoil anything
2023-08-27 RTOS tasks initialization and tweaks
2023-09-03 App redesign
    Moved RTOS implementation to Software/rtos, this further isolates
    non target specyfic code from target specyfic setup
    Basic app compiles and produces correct artifacts
2023-09-03 Task initialization
    The base of application (uC and rtos setup) is ready
2023-09-10 Lotta files small changes
    Updated FreeRTOS to the newest branch
    Added etl as external library
    Adjusting cmake scripts for multiple target builds
    clangd querry-driver option is now set for windows :(
2023-09-17 Interface for driver abstraction
2023-09-17 Unit tests and FreeRTOS mocks
    - minor improvements to Tasks
    - Mocks for xTaskCreateStatic and vTaskStartScheduler
    - Unit tests for Tasks
2023-09-19 Drv refactoring, minor improvements
2023-09-22 New hw element and CommHandler tests
2023-09-23 Tests for CommHandler
2023-09-24 Funished schematics and GPIO drv interface
2023-09-24 Some components footprint updates
2023-10-04 Layout impl start
2023-10-08 core board development
2023-10-08 Upgrade to stmg07
2023-10-16 Layout development 1
2023-10-20 Board dev + new sw target
2023-10-22 Final board schematics and sw setup
2023-10-22 Removed unnecessary libs
2023-10-29 layout dev
2023-11-04 layout dev part 2
2023-11-05 Layout dev part 3
2023-11-17 Finished Giskard layout
    - Need to fix DRC violations
    - It'd be nice to move EEPROM closer to MPU
2023-11-18 Finished board layout
2023-11-19 Final pcb adjustments
